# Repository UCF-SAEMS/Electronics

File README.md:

# Electronics
This project contains the main electronics for the SAEMS Senior Design Project. Currently, this consists of a mainboard and an secondary LED daughter board.

## Mainboard
This is the main controller board for the SAEMS project. It's main functionality is the coordination with the Zigbee base station and sensor data acquisition.

### Block Diagram

[Edit on draw.io](https://app.diagrams.net/#HUCF-SAEMS%2FElectronics%2Fmain%2Fdocs%2FSAEMS_MainbaordBlock.png)

### Schematic

### Layout
<span></span>
<span></span>

## Gerbers
Can be found within the Github [repository](build/gerbers).

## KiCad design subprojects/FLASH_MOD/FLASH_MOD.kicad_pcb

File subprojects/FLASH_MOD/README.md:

## FLASH_MOD
This is a bit of a hack. The embedded web server and coresponding assets such as html, css, and javascript libraries took more space than expected to host completly locally. To solve this problem, a FLASH_MOD was developed to add additional external flash memory over SPI.

### Schematic

### Layout
<span></span>
<span></span>

## Gerbers
Can be found within the Github [repository](build/gerbers).

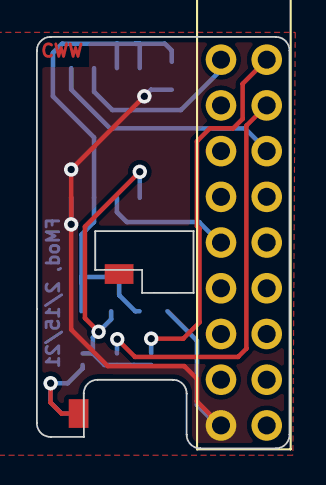
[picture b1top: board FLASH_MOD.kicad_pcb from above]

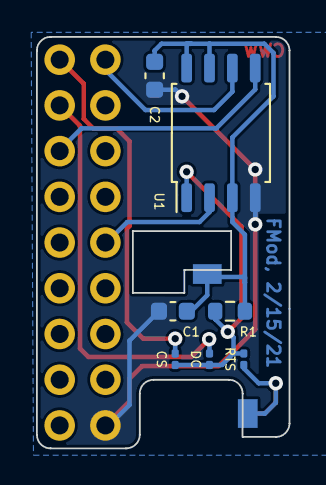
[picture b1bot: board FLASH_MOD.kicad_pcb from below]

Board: 2 copper layers, 14.0 x 22.9 mm, 10 parts (7 on the bottom side), 9 nets.

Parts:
C1: 1u; C_0603_1608Metric
C2: 0.1u; C_0603_1608Metric
JP1, JP2, JP3: Jumper_NO_Small; R_0201_0603Metric
R1: 10k; R_0603_1608Metric
TP1, TP2: TestPoint; Jumper_ModPad
U1: W25Q128JVS; SOIC-8_5.23x5.23mm_P1.27mm
U101: ER-TFTM028-4

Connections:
+3V3: C1.1, C2.1, R1.1, TP1.1, U1.3, U1.7, U1.8
/LCD_DC: JP1.1, U101.25
/WMCU_RTS: JP3.1, TP2.1
/~LCD_CS: JP2.1, U101.23
GND: C1.2, C2.2, U1.4, U101.40
unnamed: JP1.2, JP2.2, JP3.2, R1.2, U1.1
SPI_MISO: U1.2, U101.32
SPI_MOSI: U1.5, U101.27, U101.34
SPI_SCK: U1.6, U101.24, U101.33

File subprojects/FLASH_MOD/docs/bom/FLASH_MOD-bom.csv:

Row,Description,Part,References,Value,Footprint,Quantity Per PCB,Datasheet,DNP,MPN,Note,LCSC,Digikey
1,"Unpolarized capacitor, small symbol",C_Small,C2,0.1u,C_0603_1608Metric,1,~,,0603B104K500CT,CAP CER 0.1UF 50V X7R 0603,,1292-1643-1-ND
2,"Unpolarized capacitor, small symbol",C_Small,C1,1u,C_0603_1608Metric,1,~,,TMK107B7105KA-T,CAP CER 1UF 25V X7R 0603,,587-2984-1-ND
3,"Jumper, normally open, small symbol",Jumper_NO_Small,JP1 JP2 JP3,Jumper_NO_Small,R_0201_0603Metric,3,~,,,,,
4,CWW Logo,MYLIB_CWW_COPPER,LOGO101,MYLIB_CWW_COPPER,MYLIB_CWW_COPPER,1,,1,,,,
5,"Resistor, US symbol",R_US,R1,10k,R_0603_1608Metric,1,,,RC0603FR-0710KL,RES SMD 10K OHM 1% 1/10W 0603,C98220,311-10.0KHRCT-ND
6,"2.8""TFT Touch Shield for Arduino w/Capacitive Touch Screen Module",ER-TFTM028-4,U101,ER-TFTM028-4,ER-TFTM028-4,1,https://www.buydisplay.com/2-8-inch-tft-touch-shield-for-ard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,,DS1023-2*20SF11,Header Female 2x20 2.54mm,C132132,
7,"128Mb Serial Flash Memory, Standard/Dual/Quad SPI, SOIC-8",W25Q128JVS,U1,W25Q128JVS,SOIC-8_5.23x5.23mm_P1.27mm,1,http://www.winbond.com/resource-files/w25q128jv_dtr%20revc%2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,,,,,





Project info:
Schematic:,FLASH_MOD
Variant:,default
Revision:,
Date:,2021-03-14_15-13-46
KiCad Version:,5.1.7-a382d34a8~87~ubuntu18.04.1
Statistics:
Component Groups:,7
Component Count:,9
Fitted Components:,9
Number of PCBs:,1
Total Components:,9

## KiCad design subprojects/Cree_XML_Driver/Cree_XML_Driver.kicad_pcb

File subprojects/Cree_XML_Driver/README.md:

## LED Board / Cree_XML_Driver
This is the high power, RGBW LED driver and integrated module board. It includes 4 constant current buck switchers and a set WS2811's to control the individual brightnesses of each color.

### Block Diagram

[Edit on draw.io](https://app.diagrams.net/#HUCF-SAEMS%2FElectronics%2Fmain%2Fsubprojects%2FCree_XML_Driver%2Fdocs%2FSAEMS_LedDriver.png)

### Schematic

### Layout
<span></span>
<span></span>

## Gerbers
Can be found within the Github [repository](build/gerbers).

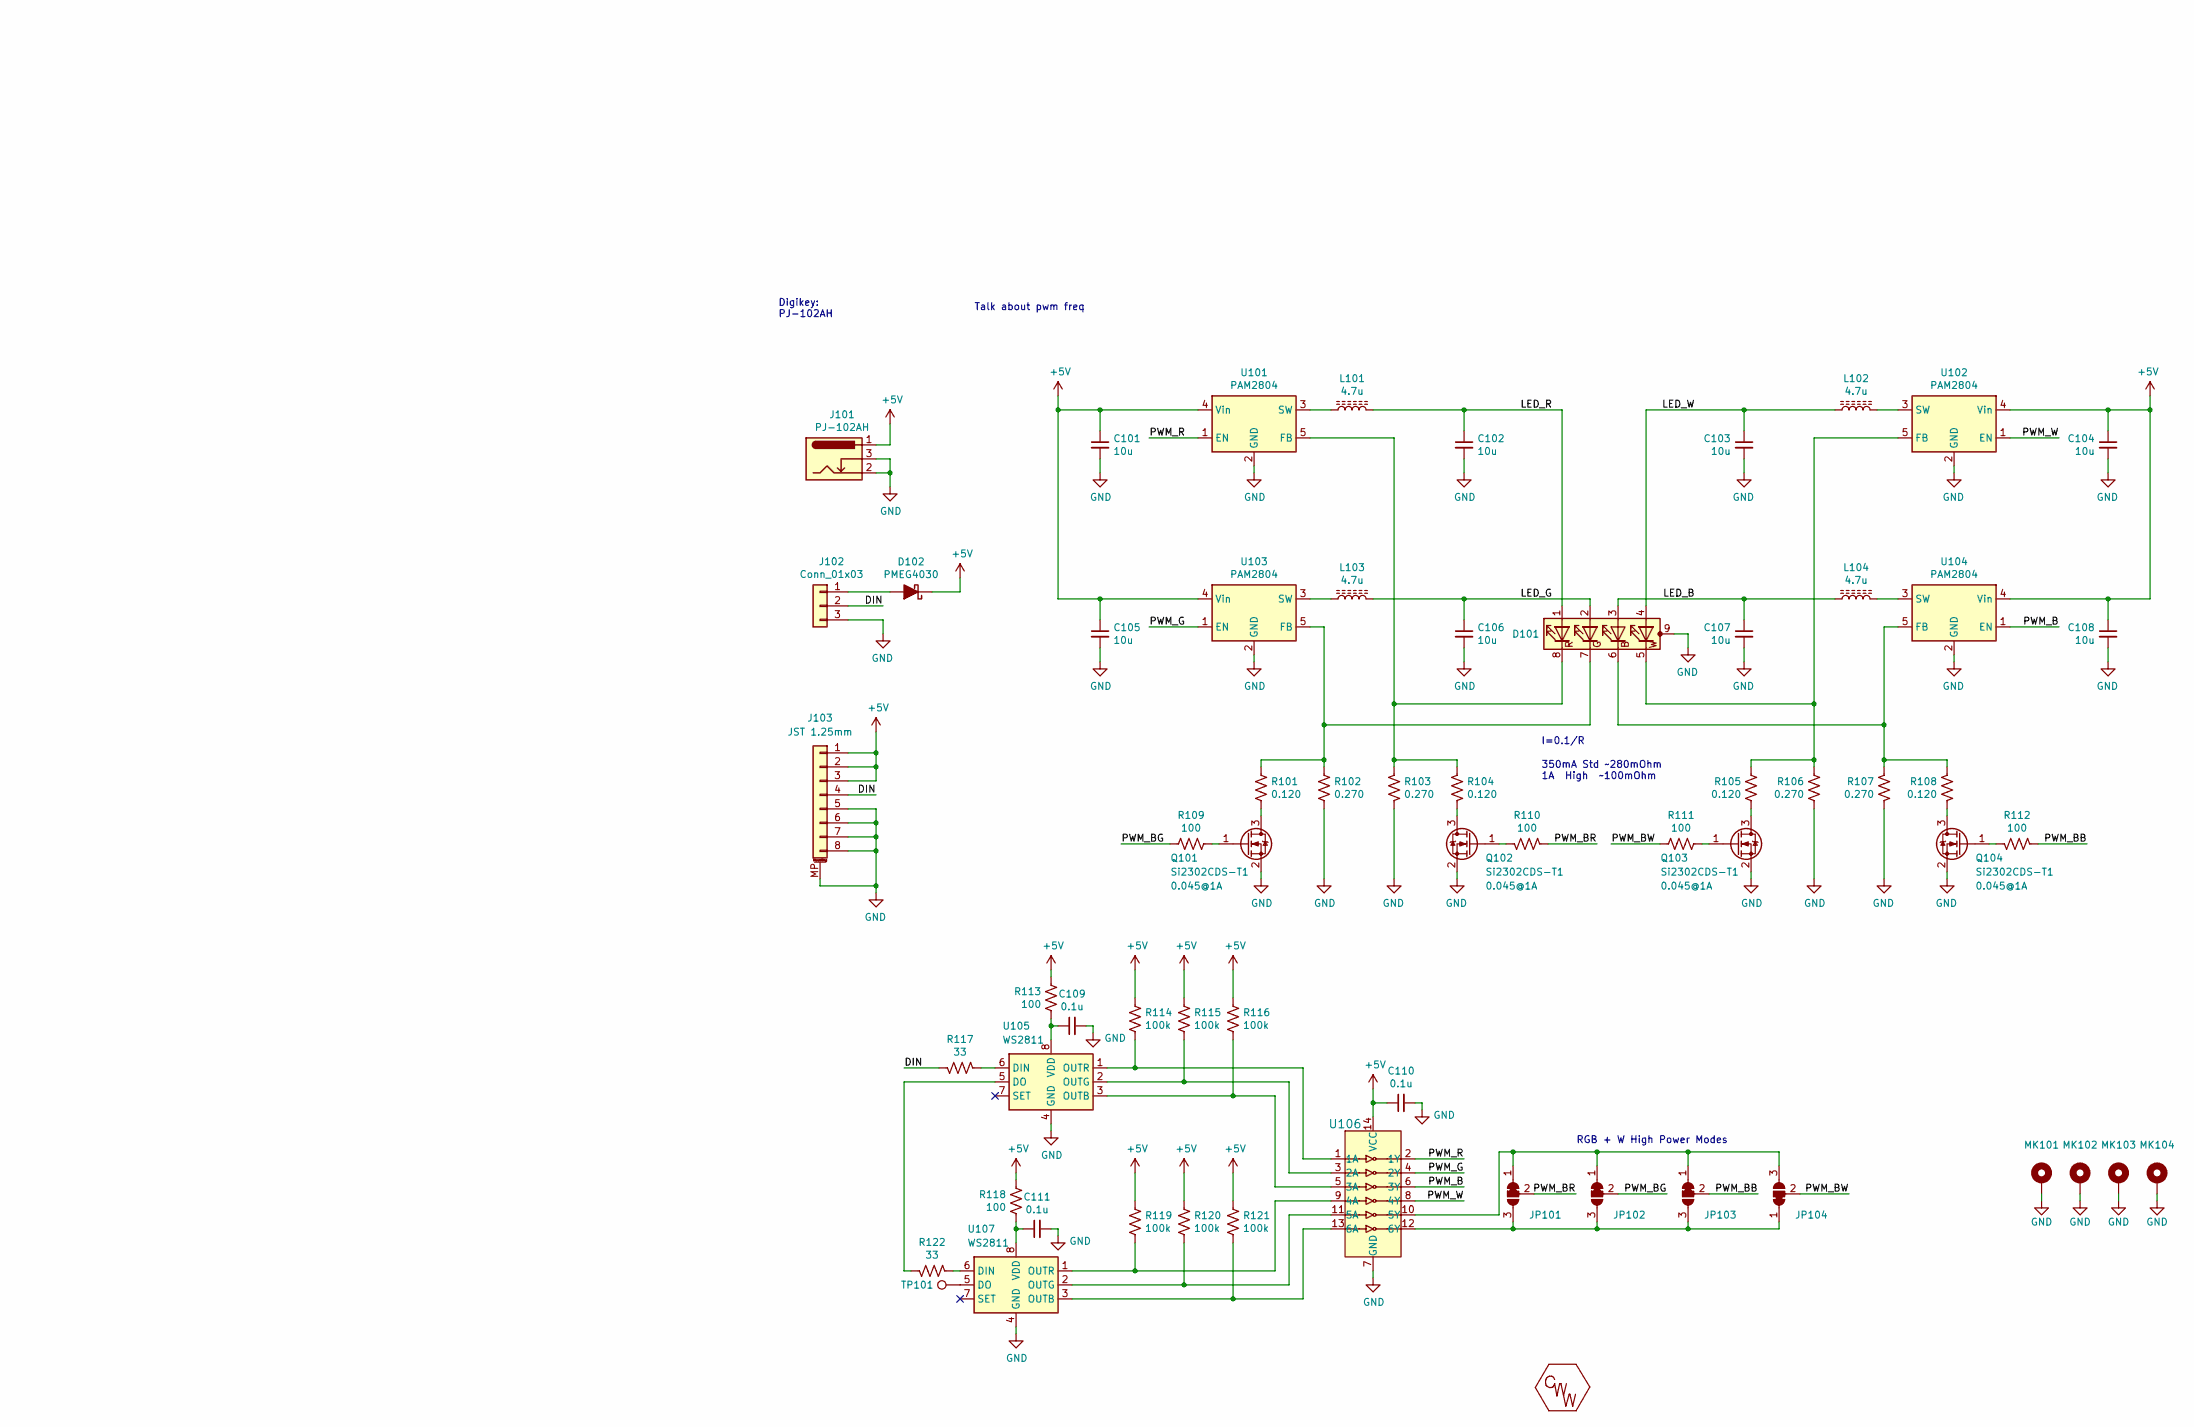
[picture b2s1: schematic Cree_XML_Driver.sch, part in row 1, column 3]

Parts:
C101, C102, C103, C104, C105, C106, C107, C108: 10u; C_0805_2012Metric; MPN GRM21BR61C106KE15L; Digikey 490-3886-1-ND
C109, C110, C111: 0.1u; C_0603_1608Metric; MPN 0603B104K500CT; Digikey 1292-1643-1-ND
D101: Cree XM-L; LED_Cree_XM-L_20mm_Module
D102: PMEG4030; D_SOD-123F; MPN PMEG4030ER,115; LCSC C389355
J101: PJ-102AH; BarrelJack_CUI_PJ-102AH_Horizontal; MPN PJ-102AH; Digikey CP-102AH-ND
J102: Conn_01x03; PinHeader_1x03_P2.54mm_Horizontal
J103: JST 1.25mm; Molex_PicoBlade_53261-0871_1x08-1MP_P1.25mm_Horizontal; MPN 0532610871; Digikey WM7626CT-ND
JP101, JP102, JP103, JP104: SolderJumper_3_Bridged12; SolderJumper-3_P1.3mm_Bridged12_Pad1.0x1.5mm
L101, L102, L103, L104: 4.7u; L_Taiyo-Yuden_MD-4040; MPN SLW4030S4R7MST; LCSC C206284, C15269
LOGO101: MYLIB_CWW_COPPER
MK101, MK102, MK103, MK104: Mounting_Hole_PAD; MountingHole_3.2mm_M3_ISO14580_Pad
Q101, Q102, Q103, Q104: Si2302CDS-T1; SOT-23; MPN Si2302CDS-T1; LCSC C10488
R101, R104, R105, R108: 0.120; R_0805_2012Metric; MPN SR732ATTDR120F; Digikey RL12S.12FCT-ND
R102, R103, R106, R107: 0.270; R_0805_2012Metric; MPN SR732ATTDR270F; Digikey RL12S.27FCT-ND
R109, R110, R111, R112, R113, R118: 100; R_0603_1608Metric; MPN RC0603FR-07100RL; Digikey 311-100HRCT-ND
R114, R115, R116, R119, R120, R121: 100k; R_0603_1608Metric; MPN RC0603FR-07100KL; Digikey 311-100KHRCT-ND
R117, R122: 33; R_0603_1608Metric; MPN RC0603FR-0733RL; Digikey 311-33.0HRCT-ND
TP101: TestPoint; TestPoint_THTPad_1.0x1.0mm_Drill0.5mm
U101, U102, U103, U104: PAM2804; TSOT-23-5; MPN PAM2804AAB010; LCSC C71463
U105, U107: WS2811; SOIC-8_3.9x4.9mm_P1.27mm; LCSC C114581
U106: 74HC14D,653; SOIC-14_3.9x8.7mm_P1.27mm; MPN 74HC14D,653; LCSC C5605

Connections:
+5V: C101.1, C104.1, C105.1, C108.1, C110.1, D102.1 (K), J101.1, J103.1, J103.2, J103.3, R113.1, R114.2, R115.2, R116.2, R118.1, R119.2, R120.2, R121.2, U101.4 (Vin), U102.4 (Vin), U103.4 (Vin), U104.4 (Vin), U106.14 (VCC)
/DIN: J102.2, J103.4, R117.2
/LED_B: C107.1, D101.3 (BA), L104.2
/LED_G: C106.1, D101.2 (GA), L103.2
/LED_R: C102.1, D101.1 (RA), L101.2
/LED_W: C103.1, D101.4 (WA), L102.2
/PWM_B: U104.1 (EN), U106.6 (3Y)
/PWM_BB: JP103.2 (C), R112.2
/PWM_BG: JP102.2 (C), R109.2
/PWM_BR: JP101.2 (C), R110.2
/PWM_BW: JP104.2 (C), R111.2
/PWM_G: U103.1 (EN), U106.4 (2Y)
/PWM_R: U101.1 (EN), U106.2 (1Y)
/PWM_W: U102.1 (EN), U106.8 (4Y)
GND: C101.2, C102.2, C103.2, C104.2, C105.2, C106.2, C107.2, C108.2, C109.2, C110.2, C111.2, D101.9 (PAD), J101.2, J101.3, J102.3, J103.5, J103.6, J103.7, J103.8, J103.MP (MountPin), MK101.1, MK102.1, MK103.1, MK104.1, Q101.2 (S), Q102.2 (S), Q103.2 (S), Q104.2 (S), R102.2, R103.2, R106.2, R107.2, U101.2 (GND), U102.2 (GND), U103.2 (GND), U104.2 (GND), U105.4 (GND), U106.7 (GND), U107.4 (GND)
unnamed: C109.1, R113.2, U105.8 (VDD)
unnamed: C111.1, R118.2, U107.8 (VDD)
unnamed: D101.5 (WK), R105.1, R106.1, U102.5 (FB)
unnamed: D101.6 (BK), R107.1, R108.1, U104.5 (FB)
unnamed: D101.7 (GK), R101.1, R102.1, U103.5 (FB)
unnamed: D101.8 (RK), R103.1, R104.1, U101.5 (FB)
unnamed: D102.2 (A), J102.1
unnamed: JP101.1 (A), JP102.1 (A), JP103.1 (A), JP104.3 (B), U106.10 (5Y)
unnamed: JP101.3 (B), JP102.3 (B), JP103.3 (B), JP104.1 (A), U106.12 (6Y)
unnamed: L101.1, U101.3 (SW)
unnamed: L102.1, U102.3 (SW)
unnamed: L103.1, U103.3 (SW)
unnamed: L104.1, U104.3 (SW)
unnamed: Q101.1 (G), R109.1
unnamed: Q101.3 (D), R101.2
unnamed: Q102.1 (G), R110.1
unnamed: Q102.3 (D), R104.2
unnamed: Q103.1 (G), R111.1
unnamed: Q103.3 (D), R105.2
unnamed: Q104.1 (G), R112.1
unnamed: Q104.3 (D), R108.2
unnamed: R114.1, U105.1 (OUTR), U106.1 (1A)
unnamed: R115.1, U105.2 (OUTG), U106.3 (2A)
unnamed: R116.1, U105.3 (OUTB), U106.5 (3A)
unnamed: R117.1, U105.6 (DIN)
unnamed: R119.1, U106.9 (4A), U107.1 (OUTR)
unnamed: R120.1, U106.11 (5A), U107.2 (OUTG)
unnamed: R121.1, U106.13 (6A), U107.3 (OUTB)
unnamed: R122.1, U107.6 (DIN)
unnamed: R122.2, U105.5 (DO)
unnamed: TP101.1, U107.5 (DO)

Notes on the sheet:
SERCOM 0
I=0.1/R
350mA Std ~~280mOhm 1A High ~~100mOhm
Digikey: PJ-102AH
Talk about pwm freq
RGB + W High Power Modes

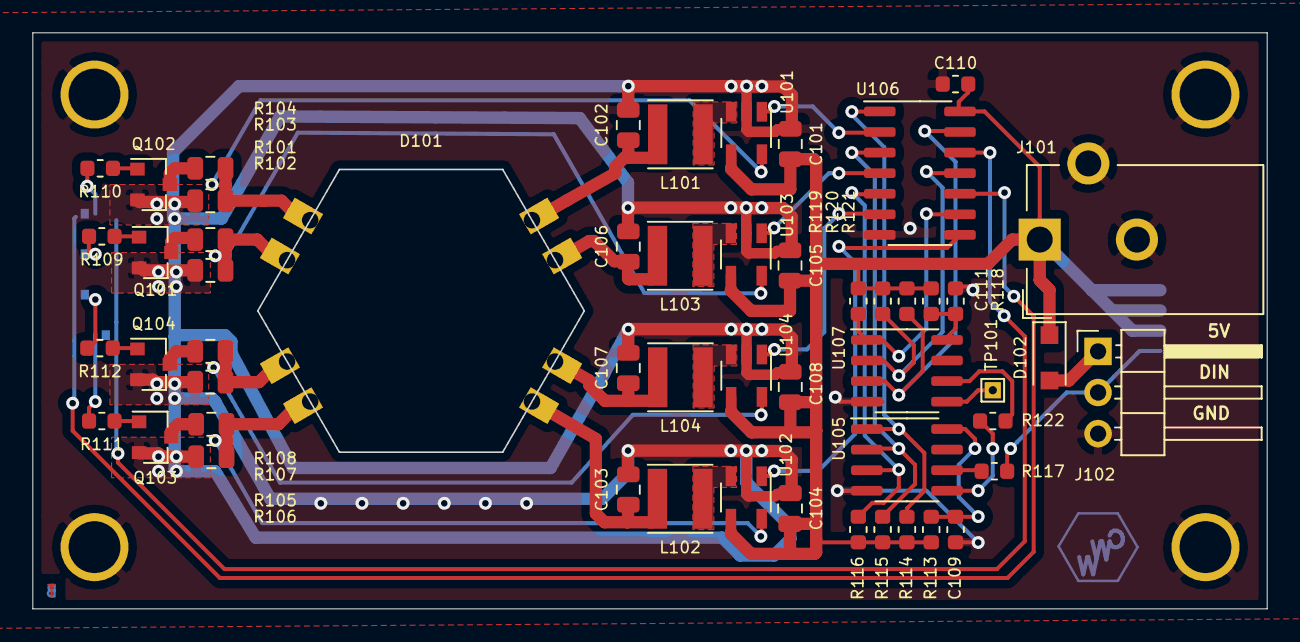
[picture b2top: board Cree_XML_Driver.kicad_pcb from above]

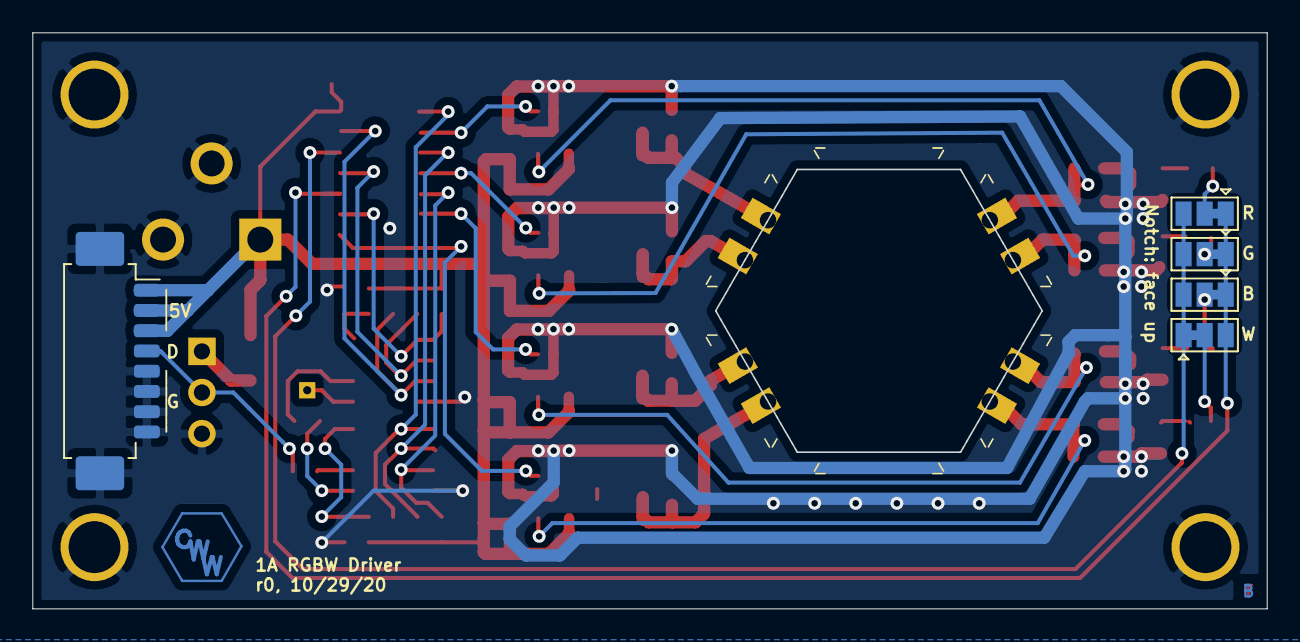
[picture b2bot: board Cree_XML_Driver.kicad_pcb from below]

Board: 2 copper layers, 76.1 x 35.5 mm, 63 parts (6 on the bottom side), 46 nets.

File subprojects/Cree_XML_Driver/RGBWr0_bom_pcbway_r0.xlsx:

|  |  | RGBW_R0 4PCS BOM
Item # | *Ref Des | *Qty | Manufacturer | *Mfg Part # | Description / Value | *Package | Type | Your Instructions / Notes | LCSC | DigiKey
1 | C106 C102 C107 C103 C104 C108 C101 C105 | 8 | Murata Electronics | GRM21BR61C106KE15L | CAP CER 10UF 16V X5R 0805 | Capacitor_SMD:C_0805_2012Metric | SMD |  | C77075 | 490-3886-1-ND
2 | C111 C110 C109 | 3 | Walsin | 0603B104K500CT | CAP CER 0.1UF 50V X7R 0603 | Capacitor_SMD:C_0603_1608Metric | SMD |  | C314282 | 1292-1643-1-ND
3 | D101 | 1 |  |  |  | mylib:LED_Cree_XM-L_20mm_Module | DNS
4 | D102 | 1 |  | PMEG4030ER,115 | DIODE SCHOTTKY 40V 3A SOD123W | Diode_SMD:D_SOD-123F | SMD |  | C389355 | 1727-5313-1-ND
5 | J101 | 1 |  | PJ-102AH | CONN PWR JACK 2X5.5MM SOLDER | Connector_BarrelJack:BarrelJack_CUI_PJ-102AH_Horizontal | DNS |  | C84007 | CP-102AH-ND
6 | J102 | 1 |  |  |  | Connector_PinHeader_2.54mm:PinHeader_1x03_P2.54mm_Horizontal | DNS
7 | J103 | 1 |  | 0532610871 | CONN HEADER SMD R/A 8POS 1.25MM | Connector_Molex:Molex_PicoBlade_53261-0871_1x08-1MP_P1.25mm_Horizontal | SMD |  | C29041 | WM7626CT-ND
8 | JP104 JP103 JP102 JP101 | 4 |  |  |  | Jumper:SolderJumper-3_P1.3mm_Bridged12_Pad1.0x1.5mm | DNS
9 | L101 L103 L102 L104 | 4 |  | SLW4030S4R7MST | 4.7uH ±20% 2A 60m Ohm SMD,4x4x3mm | Inductor_SMD:L_Taiyo-Yuden_MD-4040 | SMD | LCSC | C206284, C15269 | 587-5994-1-ND
10 | LOGO101 | 1 |  |  |  | mylib:MYLIB_CWW_COPPER | DNS
11 | MK101 MK102 MK103 MK104 | 4 |  |  |  | mylib:MountingHole_3.2mm_M3_ISO14580_Pad | DNS
12 | Q101 Q102 Q103 Q104 | 4 |  | Si2302CDS-T1 | MOSFET N-CH 20V 2.6A SOT-23 | Package_TO_SOT_SMD:SOT-23 | SMD |  | C10488 | SI2302CDS-T1-E3CT-ND
13 | R101 R104 R108 R105 | 4 |  | SR732ATTDR120F | RES 0.12 OHM 1% 1/3W 0805 | Resistor_SMD:R_0805_2012Metric | SMD | Order from Digikey | C186575, C171368 | RL12S.12FCT-ND
14 | R102 R103 R107 R106 | 4 |  | SR732ATTDR270F | RES 0.27 OHM 1% 1/3W 0805 | Resistor_SMD:R_0805_2012Metric | SMD | Order from Digikey | C186583, C171374 | RL12S.27FCT-ND
15 | R113 R118 R109 R110 R112 R111 | 6 |  | RC0603FR-07100RL | RES SMD 100 OHM 1% 1/10W 0603 | Resistor_SMD:R_0603_1608Metric | SMD |  | C105588 | 311-100HRCT-ND
16 | R114 R115 R116 R119 R120 R121 | 6 |  | RC0603FR-07100KL | RES SMD 100K OHM 1% 1/10W 0603 | Resistor_SMD:R_0603_1608Metric | SMD |  | C14675 | 311-100KHRCT-ND
17 | R117 R122 | 2 |  | RC0603FR-0733RL | RES SMD 33 OHM 1% 1/10W 0603 | Resistor_SMD:R_0603_1608Metric | SMD |  | C108661 | 311-33.0HRCT-ND
18 | TP101 | 1 |  |  |  | TestPoint:TestPoint_THTPad_1.0x1.0mm_Drill0.5mm | DNS
19 | U101 U103 U102 U104 | 4 | Diodes Incorporated | PAM2804AAB010 | IC LED DRIVER RGLTR 1A TSOT25 | Package_TO_SOT_SMD:TSOT-23-5 | SMD |  | C71463 | PAM2804AAB010DICT-ND
20 | U106 | 1 | Nexperia | 74HC14D,653 | IC INVERTER SCHMITT 6CH 14SO | Package_SO:SOIC-14_3.9x8.7mm_P1.27mm | SMD |  | C5605 | 1727-2783-1-ND
21 | U107 U105 | 2 | Worldsemi | WS2811 | IC LED DRIVER RGB | Package_SO:SOIC-8_3.9x4.9mm_P1.27mm | SMD |  | C114581
Need a quick and accurante quote? Need an efficient production? Please read SMT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
Click for Instructions on How to Create a BOM
 | for expensive parts (more than $1) please also quote LCSC and pick the cheaper.

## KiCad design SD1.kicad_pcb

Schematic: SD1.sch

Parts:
$U101: SPS30; MPN SPS30; Digikey 1649-1106-ND
C101, C103, C107: 10u; C_0603_1608Metric; MPN C1608X5R1A106M080AC; Digikey 445-6853-1-ND
C102, C104: 1u; C_0603_1608Metric; MPN TMK107B7105KA-T; Digikey 587-2984-1-ND
C105, C106, C108: 0.1u; C_0603_1608Metric; MPN 0603B104K500CT; Digikey 1292-1643-1-ND
D101: LED_RGBA; LED_19-237_1.6x1.6mm; MPN 19-237; Digikey 19-237A/R6GHBHC-B01/2T
FB101: Ferrite_Bead_Small; L_0603_1608Metric; MPN BLM18PG471SN1D; Mouser 81-BLM18PG471SN1D
J101, J102: JST 1.25mm; Molex_PicoBlade_53398-0871_1x08-1MP_P1.25mm_Vertical; MPN 0533980871; Digikey WM7612CT-ND
J103: JST ZH 1.5mm 1x5; JST-ZR-B5B-SM4-TFLFSN_1x05-1MP_P1.5mm_Vertical; MPN B5B-ZR-SM4-TF(LF)(SN); Digikey 455-1684-1-ND
JP101, JP102: SolderJumper_2_Open; SolderJumper-2_P1.3mm_Open_RoundedPad1.0x1.5mm
JP103: Jumper_NO_Small; SolderJumper-2_P1.3mm_Open_RoundedPad1.0x1.5mm
JP104: Jumper_3_Open; PinHeader_1x03_P2.54mm_Vertical
LOGO101: MYLIB_CWW_COPPER
LS101: Speaker_Crystal; Buzzer_TDK_PS1240P02BT_D12.2mm_H6.5mm; MPN PS1240P02BT; Digikey 445-2525-1-ND
MK101, MK102, MK103, MK104: Mounting_Hole_PAD; MountingHole_3.2mm_M3_ISO14580_Pad
Q101: BSS138; SOT-23; MPN BSS138; Digikey BSS138-FDICT-ND
Q102: PDTC114EU,115; SOT-323_SC-70; MPN PDTC114EU,115; LCSC C135830
R101: 100k; R_0603_1608Metric; MPN RC0603FR-07100KL; Digikey 311-100KHRCT-ND
R102, R103, R104: 1M; R_0603_1608Metric; MPN RC0603FR-071ML; Digikey 311-1.00MHRCT-ND
R105, R106, R107, R108: 10k; R_0603_1608Metric; MPN RC0603FR-0710KL; Digikey 311-10.0KHRCT-ND
R109, R110, R111, R112, R113: 1k; R_0603_1608Metric; MPN RC0603FR-071KL; Digikey 311-1.00KHRCT-ND
R114: 732k; R_0603_1608Metric; MPN RC0603FR-07732KL; Digikey 311-732KHRCT-ND
R115: 47.5k; R_0603_1608Metric; MPN RC0603FR-0747K5L; Digikey 311-47.5KHRCT-ND
SW101: Multidirection_Switch; SKRHA_bosses; MPN SKRHADE011, SKRHADE010; LCSC C602036, C202415
U101: ER-TFTM028-4; MPN DS1023-2*20SF11; LCSC C132132
U102: MCP23017; SSOP-28_5.3x10.2mm_P0.65mm; MPN MCP23017T-E/SS; Digikey MCP23017T-E/SSCT-ND
U103: CC2652P; RF-BM-2652P2; MPN RF-BM-2652P2
U104: SCD30; SCD30_reverse_mount; MPN SCD30; Digikey 1649-1098-ND
U105: BME280; Bosch_LGA-8_2.5x2.5mm_P0.65mm_ClockwisePinNumbering; MPN BME280; Digikey 828-1063-1-ND
U106: EKMC1691111; EKM; MPN EKMC1691111; Digikey 255-6303-ND

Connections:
5V_MainDet: U103.25 (DIO_24); also elsewhere on the board
+5V: $U101.1 (VDD), C107.1, J101.6, J101.7, J101.8, J102.1 (VDD), J103.5, U104.1 (VDD); also elsewhere on the board
/CO_ADC: U103.24 (DIO_23); also elsewhere on the board
/CTP_INT: U101.39 (FLASH_HOLD(CTP_INT)), U103.23 (DIO_22)
/DIO12_RXD: U103.8 (DIO_12); also elsewhere on the board
/DIO13_TXD: U103.9 (DIO_13); also elsewhere on the board
/DIO16_TDO: U103.17 (DIO_16); also elsewhere on the board
/DIO17_TDI: U103.18 (DIO_17); also elsewhere on the board
/Debug and Serial/WMCU_RTS: JP103.1; also elsewhere on the board
/ETH_CS: U103.3 (DIO_7); also elsewhere on the board
/EXT_Sleep: J102.3 (~SLEEP), U102.1 (GPB0)
/FONT_CS: U101.36 (FONT_CS), U102.3 (GPB2)
/IO_INT: U102.20 (INTA), U103.15 (DIO_14)
/I_LED_B: R112.1, U102.21 (GPA0)
/I_LED_G: R111.1, U102.22 (GPA1)
/I_LED_R: R110.1, U102.23 (GPA2)
/LCD_BACKLIGHT: R101.2, U101.29 (BL), U103.22 (DIO_21)
/LCD_DC: U101.25 (WR(D/C)), U102.4 (GPB3)
/Multi_A: SW101.1 (A), U102.24 (GPA3)
/Multi_B: SW101.2 (B), U102.25 (GPA4)
/Multi_C: SW101.3 (C), U102.26 (GPA5)
/Multi_D: SW101.6 (D), U102.27 (GPA6)
/Multi_Press: SW101.4 (Cen), U102.28 (GPA7)
/PIR_SENSE: R115.2, U103.28 (DIO_27), U106.3 (OUT)
/RGBW_DOUT: J101.5, U103.27 (DIO_26)
/SD_CS: U101.35 (SD_CS), U102.2 (GPB1)
/SPKR: JP104.3 (B), R113.1
/SPKR_Alt: JP104.1 (A), Q102.1 (B)
/SPKR_DRIVE: JP104.2 (C), U103.16 (DIO_15)
/VOC_INT: U102.7 (GPB6); also elsewhere on the board
/WMCU_CTS: U103.20 (DIO_19); also elsewhere on the board
/WMCU_RESET: U103.10 (RESET_N); also elsewhere on the board
/WMCU_RTS: JP103.2, U103.19 (DIO_18)
/WMCU_TCK: U103.12 (JTAG_TCKC); also elsewhere on the board
/WMCU_TMS: U103.11 (JTAG_TMSC); also elsewhere on the board
/~ETH_INT: U103.2 (DIO_6); also elsewhere on the board
/~ETH_RST: U102.6 (GPB5); also elsewhere on the board
/~LCD_CS: U101.23 (~LCD_CS), U103.7 (DIO_11)
/~LCD_RESET: U101.21 (~RESET), U102.5 (GPB4)
BATT_Det: U103.26 (DIO_25); also elsewhere on the board
EN_5V_BST: U102.8 (GPB7); also elsewhere on the board
GND: $U101.4 (SEL), $U101.5 (GND), C101.2, C102.1, C103.2, C104.2, C105.2, C106.2, C107.2, C108.2, J101.1, J101.2, J101.3, J101.4, J101.MP (MountPin), J102.2 (GND), J102.MP (PAD), J103.1, J103.2, J103.MP (MountPin), MK101.1, MK102.1, MK103.1, MK104.1, Q101.2 (S), Q102.2 (E), R101.1, R103.2, R107.2, R114.1, R115.1, SW101.5 (Com), U101.1 (VSS), U101.40 (VSS), U102.10 (VSS), U103.14 (GND), U104.2 (GND), U104.7 (SEL), U105.1 (GND), U105.7 (GND), U106.1 (GND); also elsewhere on the board
I2C_SCL: $U101.3 (TX/SCL), J102.4 (-->RXD/SCL), J103.3, R106.2, U101.30 (RTP_CS(CTP_SCL)), U102.12 (SCK), U103.21 (DIO_20), U104.3 (TX/SCL), U105.4 (SCK); also elsewhere on the board
I2C_SDA: $U101.2 (RX/SDA), J102.5 (<--TXD/SDA), J103.4, R105.2, U101.31 (RTP_PEN(CTP_SDA)), U102.13 (SDA), U103.1 (DIO_5), U104.4 (RX/SDA), U105.3 (SDI); also elsewhere on the board
unnamed: C106.1, FB101.1, U105.8 (VDD)
unnamed: D101.1 (RK), R110.2
unnamed: D101.2 (GK), R111.2
unnamed: D101.3 (BK), R112.2
unnamed: JP101.1 (A), U101.26 (RD)
unnamed: JP102.1 (A), U101.28 (LCD_SDO)
unnamed: LS101.2, Q101.3 (D), Q102.3 (C), R109.1
unnamed: Q101.1 (G), R113.2, R114.2
unnamed: R102.2, U102.18 (~RESET~)
unnamed: R103.1, U102.16 (A1), U102.17 (A2)
unnamed: R104.1, U102.15 (A0)
unnamed: R107.1, U105.5 (SDO)
unnamed: R108.1, U105.2 (CSB)
SPI_MISO: JP102.2 (B), U101.32 (SDO), U103.4 (DIO_8); also elsewhere on the board
SPI_MOSI: U101.27 (LCD_SDI(SDA)), U101.34 (SDI), U103.5 (DIO_9); also elsewhere on the board
SPI_SCK: U101.24 (LCD_D/C(SCL)), U101.33 (SCL), U103.6 (DIO_10); also elsewhere on the board

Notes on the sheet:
SERCOM 0
Barrel Jack: 5.5mm OD 2.1mm ID/Pole
See 21.4.4
The Serial 4wire SPI MCU interface I Reference Example
See: https://www.buydisplay.com/download/interfacing/ER-TFT028-4_CTP_Interfacing.pdf
See: https://www.buydisplay.com/download/interfacing/ER-TFTM028-4_Interfacing.pdf
Use 33k - 100k
Need to flip bc of cable
I2C: 111011[0][rw]
Particulates
Temp / Humidity / Pressure
Motion Detection
External / Additional Sensor Connector
Carbon Monoxide Sensor
Carbon Dioxide Sensor
Volatile Organic Compounds
Smoke Sensor
Buy 2x40 display header, PRT-16764
Need Jumper

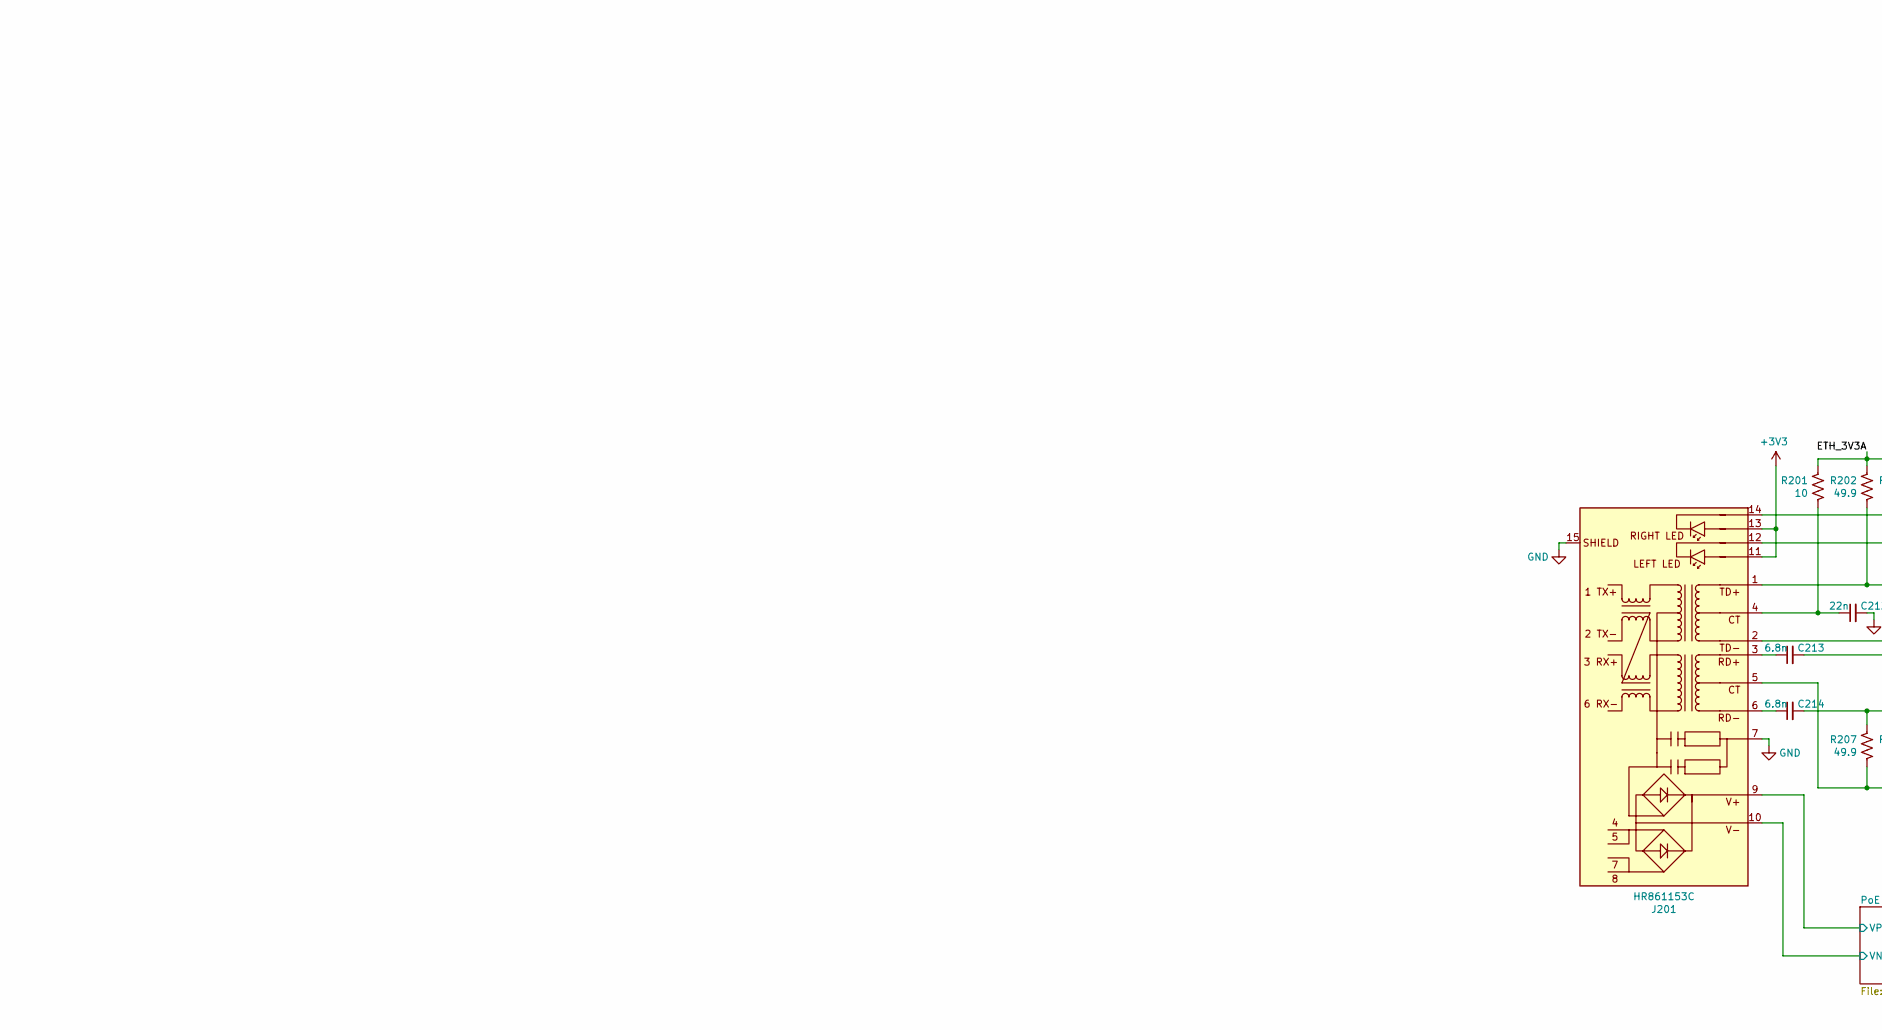
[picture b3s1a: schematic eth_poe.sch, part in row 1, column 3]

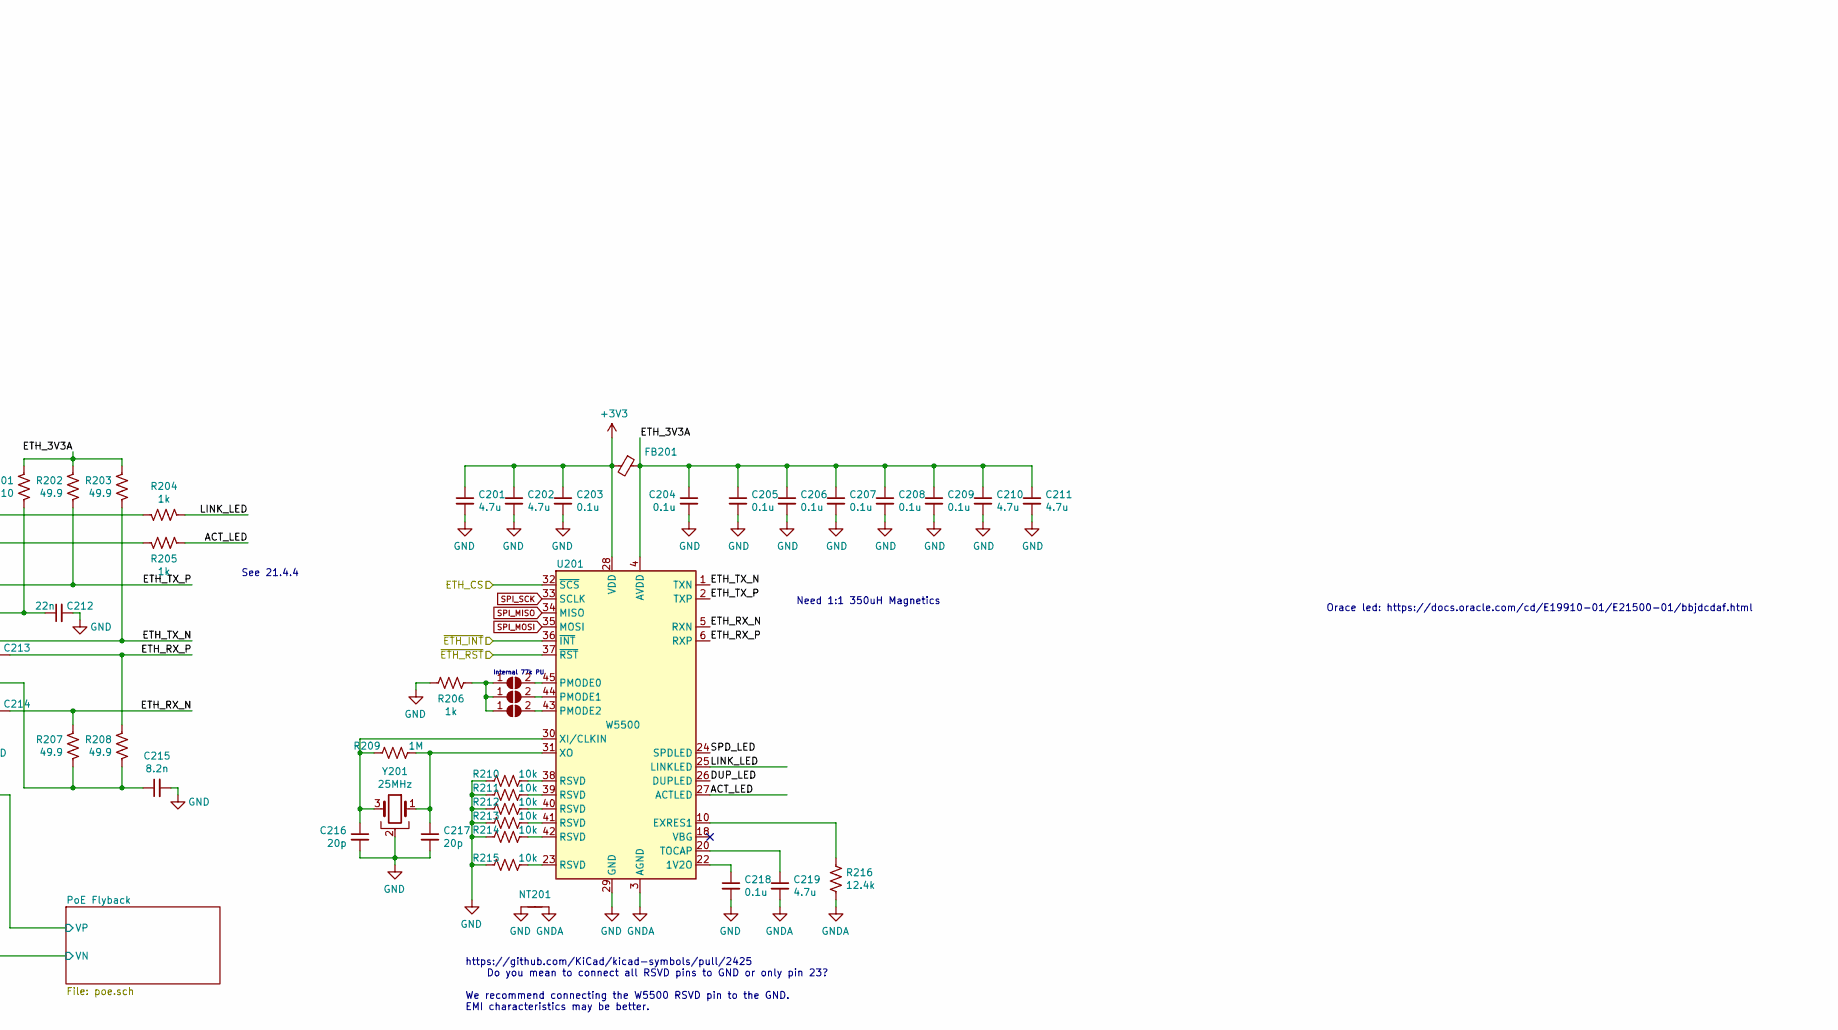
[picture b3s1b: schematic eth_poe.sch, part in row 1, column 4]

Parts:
C201, C202, C210, C211, C219: 4.7u; C_0603_1608Metric; MPN C0603C475K9PACTU; Digikey 399-3482-1-ND
C203, C204, C205, C206, C207, C208, C209, C218: 0.1u; C_0603_1608Metric; MPN 0603B104K500CT; Digikey 1292-1643-1-ND
C212: 22n; C_0603_1608Metric; MPN CL10B223KC8WPNC; Digikey 1276-CL10B223KC8WPNCCT-ND
C213, C214: 6.8n; C_0603_1608Metric; MPN CC0603KRX7R9BB682; Digikey 311-1084-1-ND
C215: 8.2n; C_0603_1608Metric; Voltage 50V; MPN CC0603KRX7R9BB822; Digikey 311-1811-1-ND
C216, C217: 20p; C_0603_1608Metric; MPN CC0603JRNPO9BN200; Digikey 311-1424-1-ND
FB201: Ferrite_Bead_Small; L_0603_1608Metric; MPN BLM18PG471SN1D; Digikey 490-5223-1-ND
J201: HR861153C; RJ45_Abracon_ARJP11A-MA_Horizontal; MPN ARJP11A-MASA-B-A-EMU2; Digikey ARJP11A-MASA-B-A-EMU2-ND
JP201, JP202, JP203: SolderJumper_2_Open; R_0201_0603Metric
NT201: Net-Tie_2; NetTie-2_SMD_Pad0.5mm
R201: 10; R_0603_1608Metric; MPN RC0603JR-0710RL; Digikey 311-10GRDKR-ND
R202, R203, R207, R208: 49.9; R_0603_1608Metric
R204, R205, R206: 1k; R_0603_1608Metric; MPN RC0603FR-071KL; Digikey 311-1.00KHRCT-ND
R209: 1M; R_0603_1608Metric; MPN RC0603FR-071ML; Digikey 311-1.00MHRCT-ND
R210, R211, R212, R213, R214, R215: 10k; R_0603_1608Metric; MPN RC0603FR-0710KL; Digikey 311-10.0KHRCT-ND
R216: 12.4k; R_0603_1608Metric; MPN RC0603FR-0712K1L; Digikey 311-12.1KHRCT-ND
U201: W5500; LQFP-48_7x7mm_P0.5mm; MPN W5500; Digikey 1278-1021-ND
Y201: 25MHz; Crystal_SMD_3225-4Pin_3.2x2.5mm; MPN X1E000021035200; Digikey SER4375CT-ND

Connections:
/ETH_CS: U201.32 (~SCS); also elsewhere on the board
/Eth + PoE/ACT_LED: R205.1, U201.27 (ACTLED)
/Eth + PoE/ETH_3V3A: C204.1, C205.1, C206.1, C207.1, C208.1, C209.1, C210.1, C211.1, FB201.1, R201.2, R202.2, R203.2, U201.4 (AVDD), U201.8 (AVDD), U201.11 (AVDD), U201.15 (AVDD), U201.17 (AVDD), U201.21 (AVDD)
/Eth + PoE/ETH_RX_N: C214.2, R207.2, U201.5 (RXN)
/Eth + PoE/ETH_RX_P: C213.2, R208.2, U201.6 (RXP)
/Eth + PoE/ETH_TX_N: J201.2 (TD-), R203.1, U201.1 (TXN)
/Eth + PoE/ETH_TX_P: J201.1 (TD+), R202.1, U201.2 (TXP)
/Eth + PoE/LINK_LED: R204.1, U201.25 (LINKLED)
/Eth + PoE/PoE Flyback/VN: J201.10 (V-); also elsewhere on the board
/Eth + PoE/PoE Flyback/VP: J201.9 (V+); also elsewhere on the board
/~ETH_INT: U201.36 (~INT); also elsewhere on the board
/~ETH_RST: U201.37 (~RST); also elsewhere on the board
GND: C201.2, C202.2, C203.2, C204.2, C205.2, C206.2, C207.2, C208.2, C209.2, C210.2, C211.2, C212.2, C215.2, C216.2, C217.2, C218.2, J201.7, J201.15 (SHIELD), NT201.1, R206.1, R210.1, R211.1, R212.1, R213.1, R214.1, R215.1, U201.29 (GND), Y201.2; also elsewhere on the board
GNDA: C219.2, NT201.2, R216.1, U201.3 (AGND), U201.9 (AGND), U201.14 (AGND), U201.16 (AGND), U201.19 (AGND), U201.48 (AGND); also elsewhere on the board
unnamed: C212.1, J201.4 (CT), R201.1
unnamed: C213.1, J201.3 (RD+)
unnamed: C214.1, J201.6 (RD-)
unnamed: C215.1, J201.5 (CT), R207.1, R208.1
unnamed: C216.1, R209.2, U201.30 (XI/CLKIN), Y201.3
unnamed: C217.1, R209.1, U201.31 (XO), Y201.1
unnamed: C218.1, U201.22 (1V2O)
unnamed: C219.1, U201.20 (TOCAP)
unnamed: J201.12 (LLED-), R205.2
unnamed: J201.14 (RLED-), R204.2
unnamed: JP201.1 (A), JP202.1 (A), JP203.1 (A), R206.2
unnamed: JP201.2 (B), U201.45 (PMODE0)
unnamed: JP202.2 (B), U201.44 (PMODE1)
unnamed: JP203.2 (B), U201.43 (PMODE2)
unnamed: R210.2, U201.38 (RSVD)
unnamed: R211.2, U201.39 (RSVD)
unnamed: R212.2, U201.40 (RSVD)
unnamed: R213.2, U201.41 (RSVD)
unnamed: R214.2, U201.42 (RSVD)
unnamed: R215.2, U201.23 (RSVD)
unnamed: R216.2, U201.10 (EXRES1)
SPI_MISO: U201.34 (MISO); also elsewhere on the board
SPI_MOSI: U201.35 (MOSI); also elsewhere on the board
SPI_SCK: U201.33 (SCLK); also elsewhere on the board

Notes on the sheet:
SERCOM 0
See 21.4.4
Orace led: https://docs.oracle.com/cd/E19910-01/E21500-01/bbjdcdaf.html
Internal 77k PU
Need 1:1 350uH Magnetics
https://github.com/KiCad/kicad-symbols/pull/2425 Do you mean to connect all RSVD pins to GND or only pin 23? We recommend connecting the W5500 RSVD pin to the GND. EMI characteristics may be better.
